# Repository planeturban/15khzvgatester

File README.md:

# 15khzvgatester

It's free.

Based on Nick Gammons work: http://www.gammon.com.au/forum/?id=11608

# Notes

Make sure your vias are covered othervise you'll probably connect them to the battery's GND.

{:height="50%" width="50%"}

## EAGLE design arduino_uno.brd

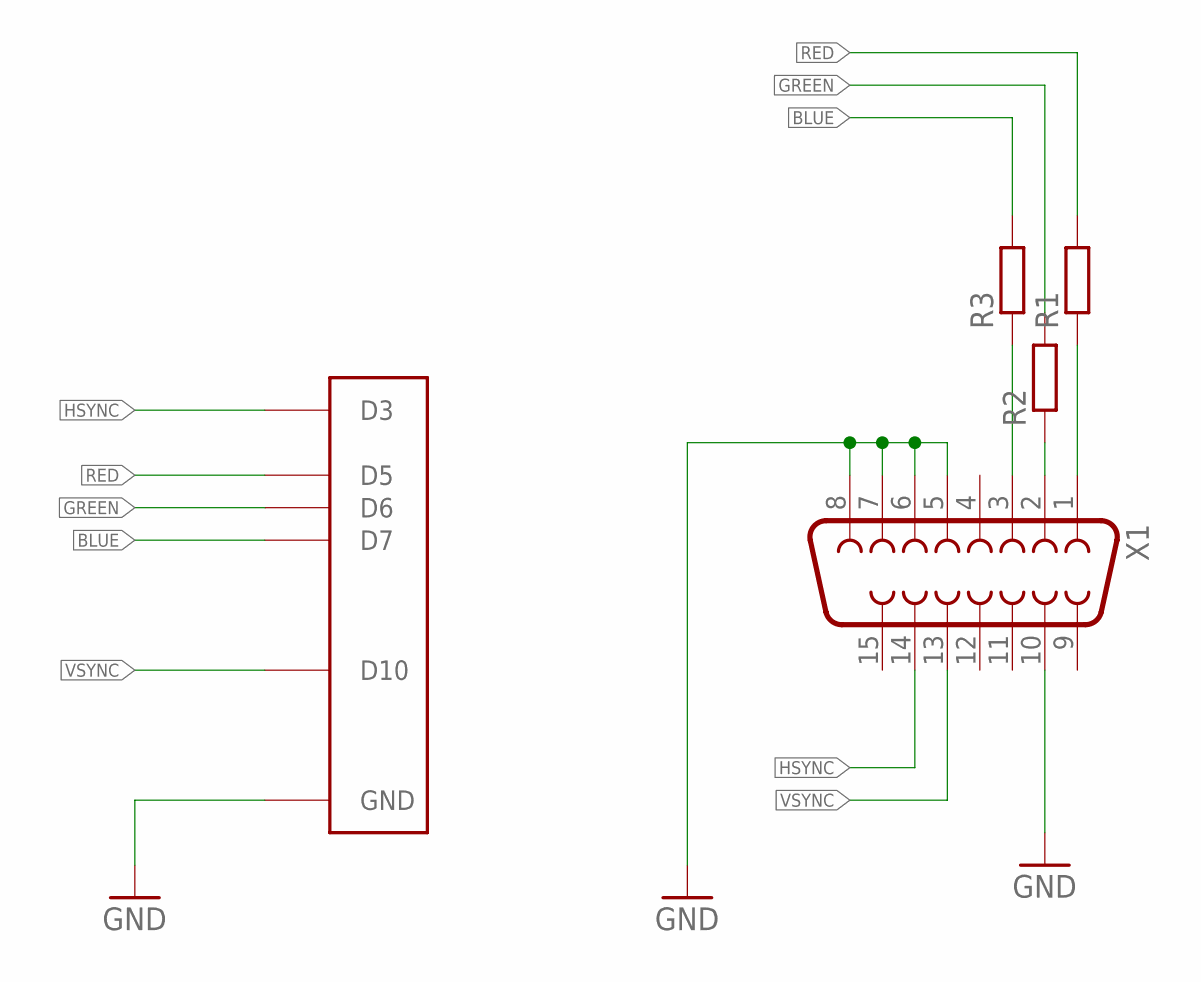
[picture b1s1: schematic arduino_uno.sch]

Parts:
R1, R2, R3: R-EU_0207/10; 0207/10
U$1: ARDUINOUNO; ARDUINO
X1: F15HDV; HDF15V

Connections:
BLUE: R3.2, U$1.D7
GND: U$1.GND, X1.5, X1.6, X1.7, X1.8, X1.10
GREEN: R2.2, U$1.D6
HSYNC: U$1.D3, X1.14
unnamed: R1.1, X1.1
unnamed: R2.1, X1.2
unnamed: R3.1, X1.3
RED: R1.2, U$1.D5
VSYNC: U$1.D10, X1.13

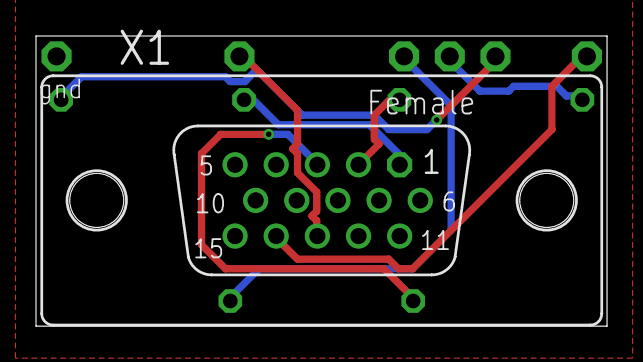
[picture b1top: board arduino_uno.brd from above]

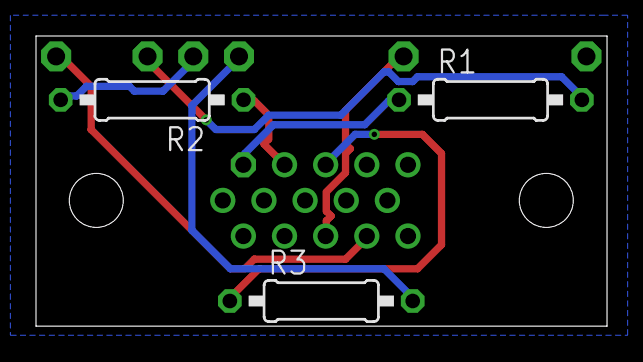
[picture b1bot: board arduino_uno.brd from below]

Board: 2 copper layers, 31.7 x 16.1 mm, 5 parts (3 on the bottom side), 9 nets.

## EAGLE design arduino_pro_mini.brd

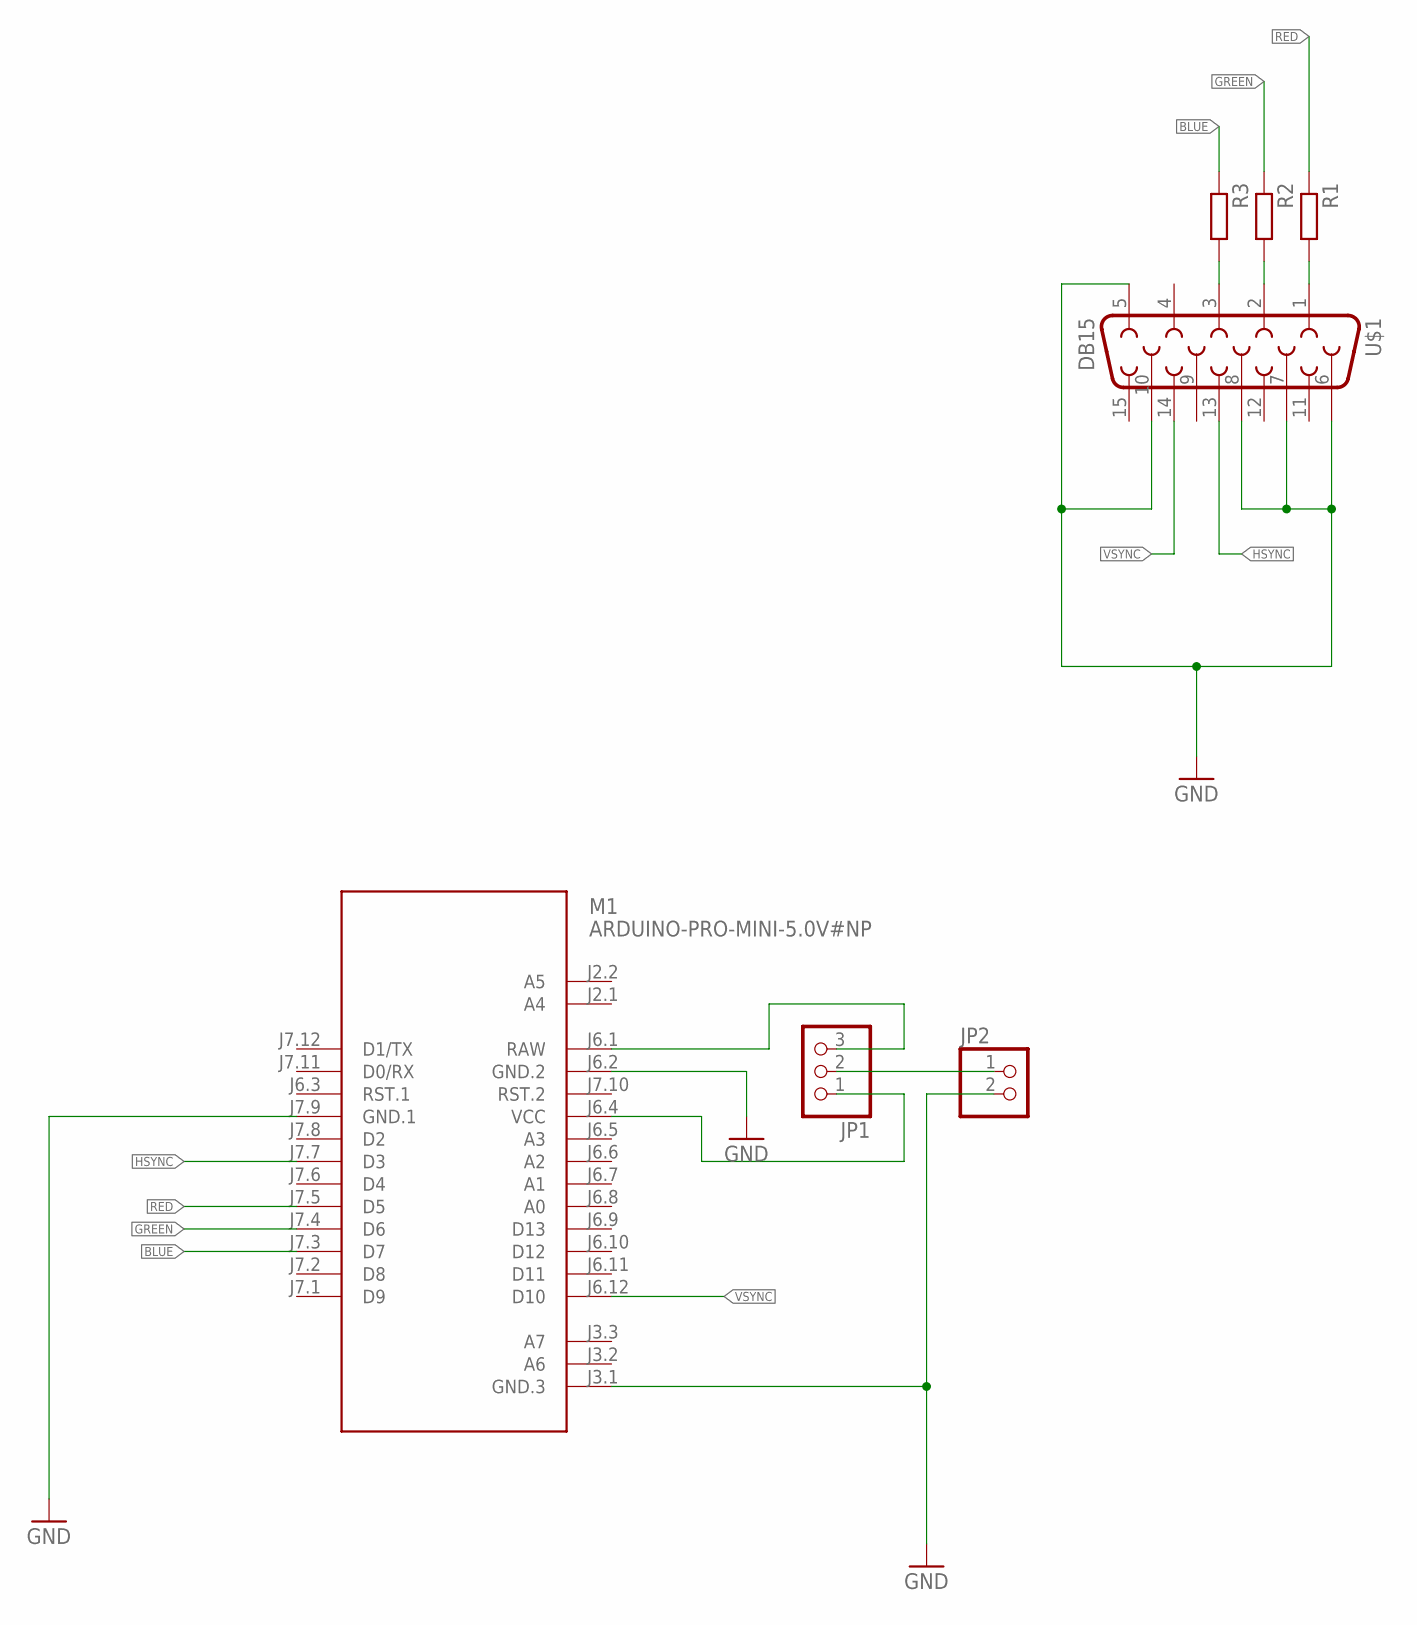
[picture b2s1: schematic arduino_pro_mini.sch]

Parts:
JP1: PINHD-1X3/90; 1X03/90
JP2: PINHD-1X2; 1X02
M1: ARDUINO-PRO-MINI-5.0V#NP; ARDUINO-PRO-MINI#NP
R1, R2, R3: R-EU_0207/10; 0207/10
U$1: DB15

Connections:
BLUE: M1.J7.3 (D7), R3.1
GND: JP2.2, M1.J3.1 (GND.3), M1.J6.2 (GND.2), M1.J7.9 (GND.1), U$1.5, U$1.6, U$1.7, U$1.8, U$1.10
GREEN: M1.J7.4 (D6), R2.1
HSYNC: M1.J7.7 (D3), U$1.13
unnamed: JP1.1, M1.J6.4 (VCC)
unnamed: JP1.3, M1.J6.1 (RAW)
unnamed: JP1.2, JP2.1
unnamed: R3.2, U$1.3
unnamed: R2.2, U$1.2
unnamed: R1.2, U$1.1
RED: M1.J7.5 (D5), R1.1
VSYNC: M1.J6.12 (D10), U$1.14

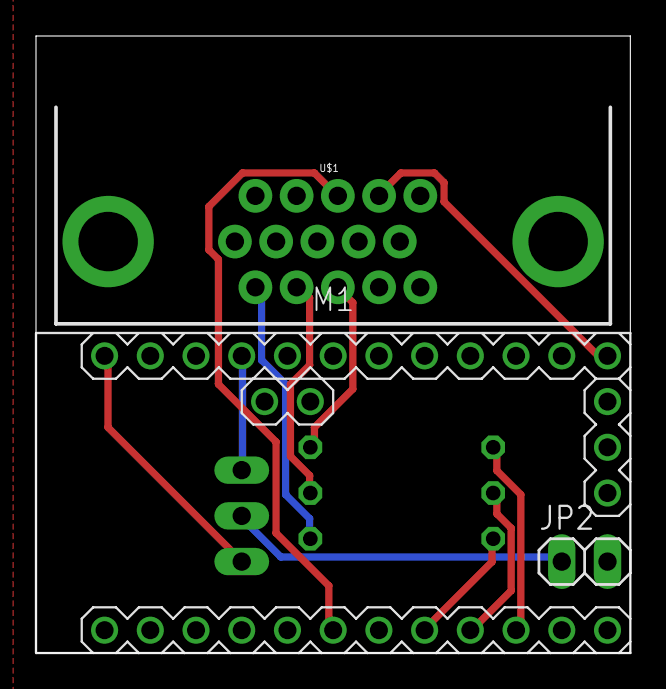
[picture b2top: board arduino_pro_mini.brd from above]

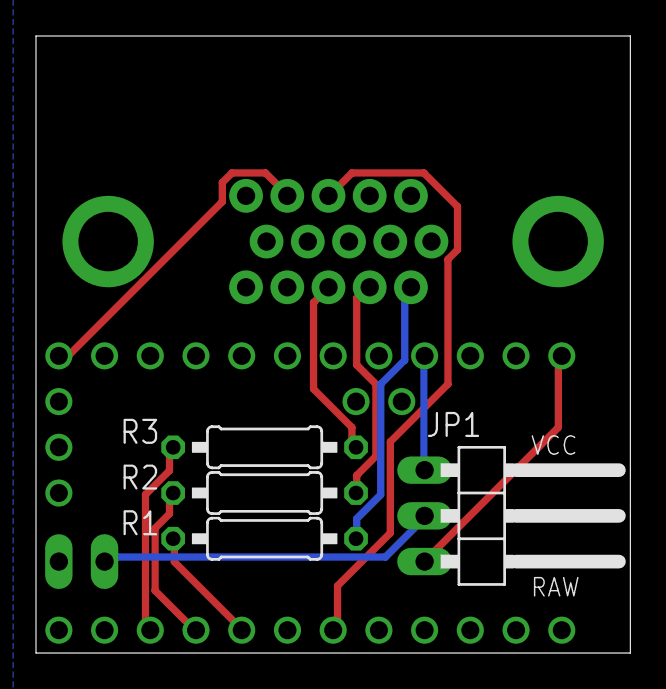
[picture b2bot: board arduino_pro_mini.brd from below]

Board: 2 copper layers, 33.0 x 34.3 mm, 7 parts (4 on the bottom side), 12 nets.

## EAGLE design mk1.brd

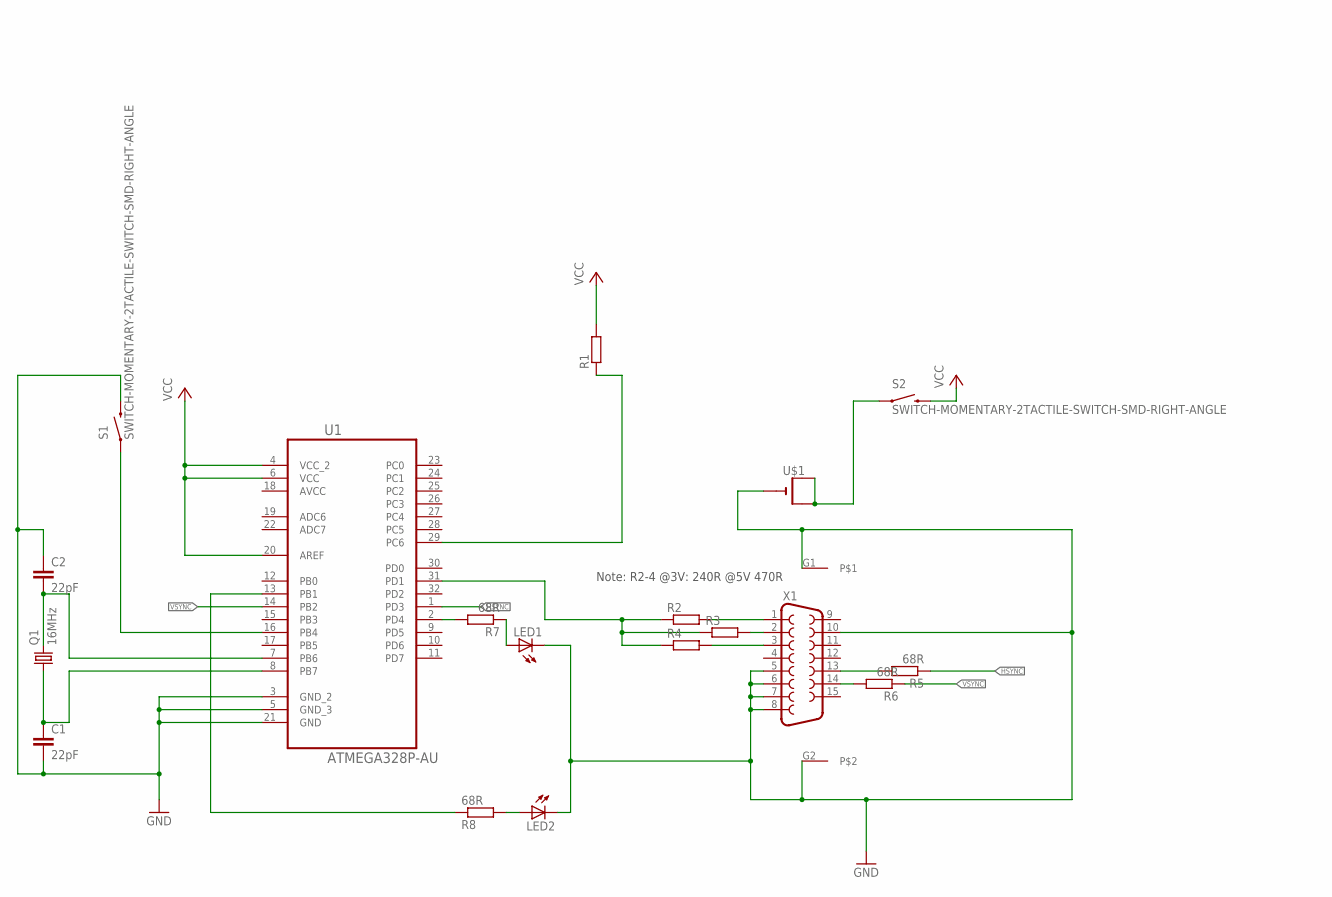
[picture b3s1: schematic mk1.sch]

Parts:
C1, C2: 22pF; C1206
LED1, LED2: LEDCHIPLED_1206; CHIPLED_1206
Q1: 16MHz; HC49UP
R1, R2, R3, R4: R-EU_M1206; M1206
R5, R6, R7, R8: 68R; M1206
S1, S2: SWITCH-MOMENTARY-2TACTILE-SWITCH-SMD-RIGHT-ANGLE; TACTILE_SWITCH-SMD-RIGHT-ANGLE
U1: ATMEGA328P-AU; QFP80P900X900X120-32N
U$1: CR2032SMT; CR2032-SMD
X1: F15HDV; HDF15V

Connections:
AVCC: U1.18 (AVCC)
GND: C1.2, C2.1, LED1.C, LED2.C, S1.2, U1.3 (GND_2), U1.5 (GND_3), U1.21 (GND), U$1.-, X1.5, X1.6, X1.7, X1.8, X1.10, X1.G1, X1.G2
HSYNC: R5.1, U1.1 (PD3)
unnamed: R7.2, U1.2 (PD4)
unnamed: R8.1, U1.13 (PB1)
unnamed: R2.1, R3.1, R4.1, U1.31 (PD1)
unnamed: LED1.A, R7.1
unnamed: LED2.A, R8.2
unnamed: R2.2, X1.1
unnamed: R3.2, X1.2
unnamed: R4.2, X1.3
unnamed: R6.2, X1.14
unnamed: R5.2, X1.13
unnamed: S1.1, U1.16 (PB4)
PWR: S2.1, U$1.+$1 (+), U$1.+$2 (+1)
RESET: R1.1, U1.29 (PC6)
VCC: R1.2, S2.2, U1.4 (VCC_2), U1.6 (VCC), U1.20 (AREF)
VSYNC: R6.1, U1.14 (PB2)
XTAL1: C1.1, Q1.1, U1.8 (PB7)
XTAL2: C2.2, Q1.2, U1.7 (PB6)

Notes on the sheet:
Note: R2-4 @3V: 240R @5V 470R

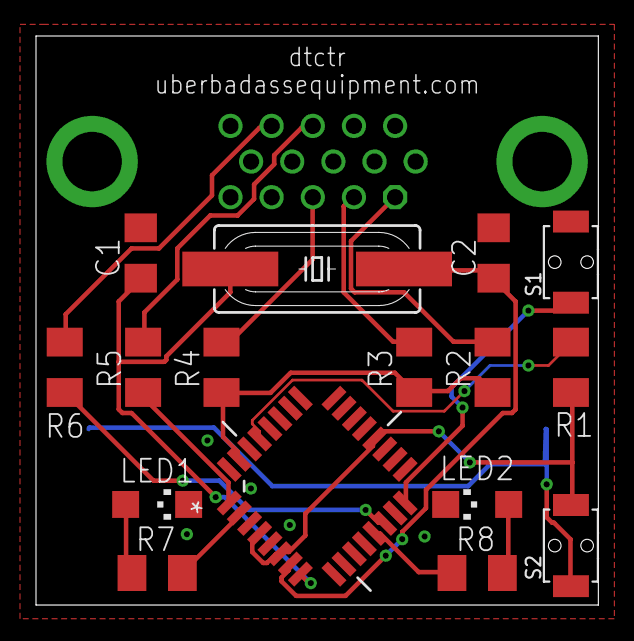
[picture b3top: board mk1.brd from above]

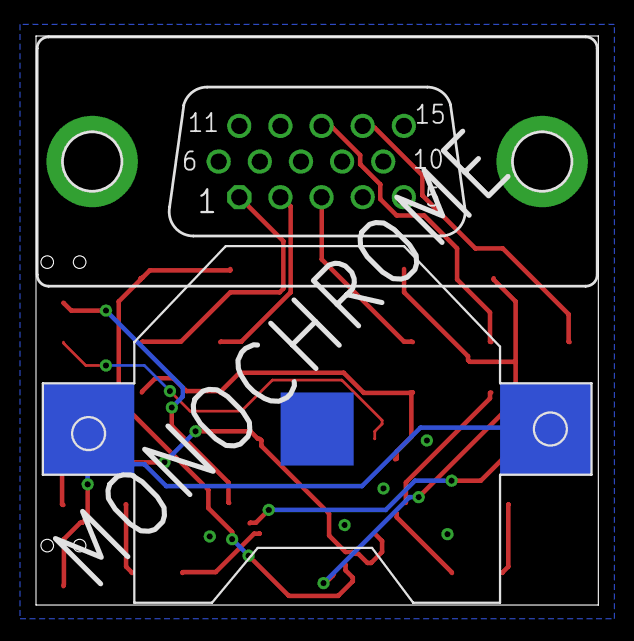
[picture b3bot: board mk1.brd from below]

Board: 2 copper layers, 31.2 x 31.6 mm, 18 parts (2 on the bottom side), 19 nets.

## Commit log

2017-12-13 First
2017-12-13 Added code, needs tuning.
2017-12-13 gitignore
2017-12-15 Create LICENSE
2017-12-17 Some cleanup. Moved battery holder, less risk of shorting the battery. Changed pins for LEDs for easier routing.
2017-12-17 Color version. NOT tested with 3V. Added a 78L05 and external power.
2018-01-06 Color is confirmed working.
2018-01-06 Some cleanup.
2018-01-06 Added some text.
2018-01-06 Added Arduino shields, mk2
2018-01-07 Schematics cleanup. Less aaaaaaah.

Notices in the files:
parts and their libraries:
diy-modules: Released under the Creative Commons Attribution 4.0 International License: http://creativecommons.org/licenses/by/4.0
SparkFun-Connectors: Licensing: Creative Commons ShareAlike 4.0 International - https://creativecommons.org/licenses/by-sa/4.0
